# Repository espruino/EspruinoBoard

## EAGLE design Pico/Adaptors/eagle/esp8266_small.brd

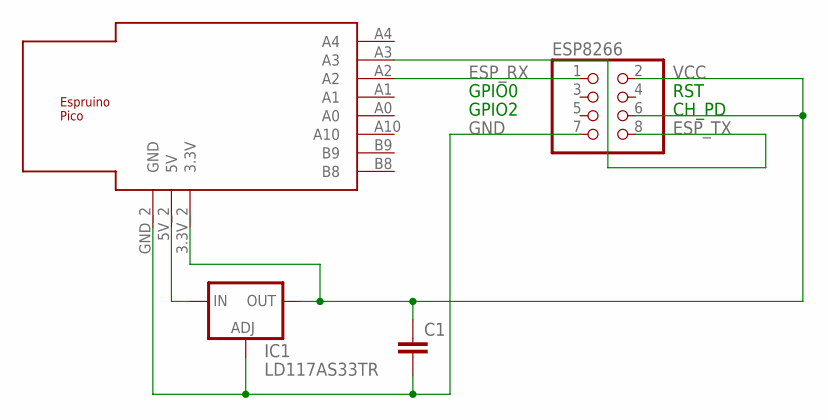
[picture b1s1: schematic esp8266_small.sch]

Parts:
C1: C-EUC1210; C1210
ESP8266: PINHD-2X4; 2X04
IC1: LD117AS33TR; SOT223
U$1: ESPRUINO_PICO_0.05

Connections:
ESP_RX: ESP8266.1, U$1.A2
ESP_TX: ESP8266.8, U$1.A3
GND: C1.2, ESP8266.7, IC1.1 (ADJ), U$1.GND_2 (GND)
unnamed: IC1.3 (IN), U$1.5V_2 (5V)
VCC: C1.1, ESP8266.2, ESP8266.6, IC1.4 (OUT), U$1.3.3V_2 (3.3V)

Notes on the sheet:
CH_PD
RST
GPIO0
GPIO2

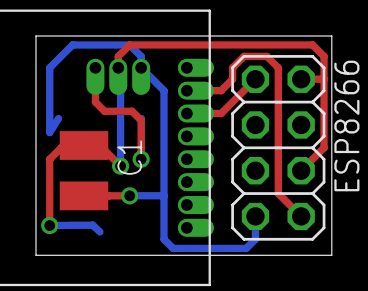
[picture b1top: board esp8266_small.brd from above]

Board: 2 copper layers, 16.4 x 12.2 mm, 4 parts (1 on the bottom side), 5 nets.

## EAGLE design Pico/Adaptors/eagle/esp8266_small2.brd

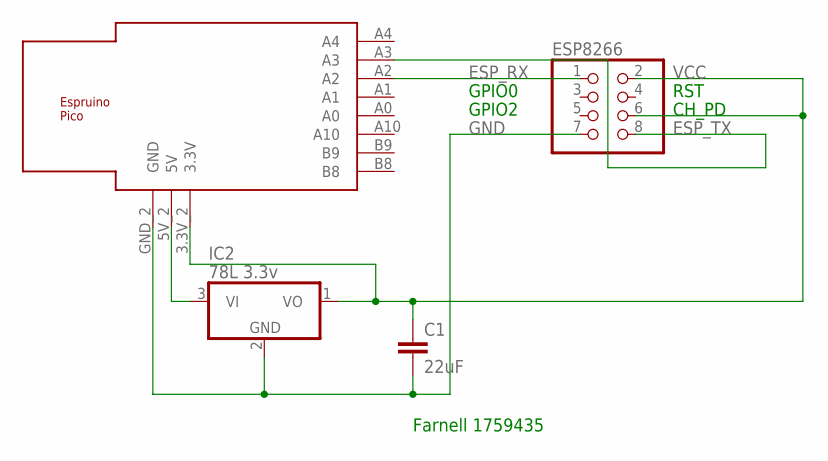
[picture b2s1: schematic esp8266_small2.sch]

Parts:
C1: 22uF; C1210
ESP8266: PINHD-2X4; 2X04
IC2: 78L 3.3v; TO92
U$1: ESPRUINO_PICO_0.05

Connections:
ESP_RX: ESP8266.1, U$1.A2
ESP_TX: ESP8266.8, U$1.A3
GND: C1.2, ESP8266.7, IC2.2 (GND), U$1.GND_2 (GND)
unnamed: IC2.3 (VI), U$1.5V_2 (5V)
VCC: C1.1, ESP8266.2, ESP8266.6, IC2.1 (VO), U$1.3.3V_2 (3.3V)

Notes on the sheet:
CH_PD
RST
GPIO0
GPIO2
Farnell 1759435

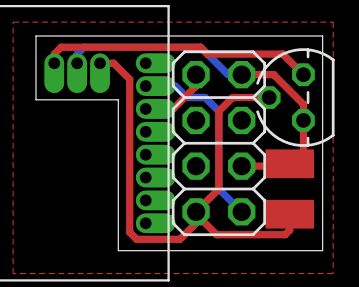
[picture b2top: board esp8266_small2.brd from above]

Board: 2 copper layers, 15.9 x 11.9 mm, 4 parts (0 on the bottom side), 5 nets.

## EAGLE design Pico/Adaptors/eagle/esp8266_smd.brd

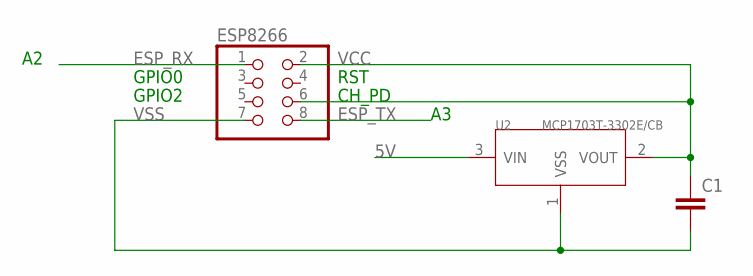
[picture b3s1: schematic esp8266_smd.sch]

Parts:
C1: C-EU025-050X050; C025-050X050
ESP8266: PINHD-2X4; 2X04
U2: MCP1703T-3302E/CB; SOT23

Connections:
5V: U2.3 (VIN)
ESP_RX: ESP8266.1
ESP_TX: ESP8266.8
VCC: C1.1, ESP8266.2, ESP8266.6, U2.2 (VOUT)
VSS: C1.2, ESP8266.7, U2.1 (VSS)

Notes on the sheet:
CH_PD
RST
GPIO0
GPIO2

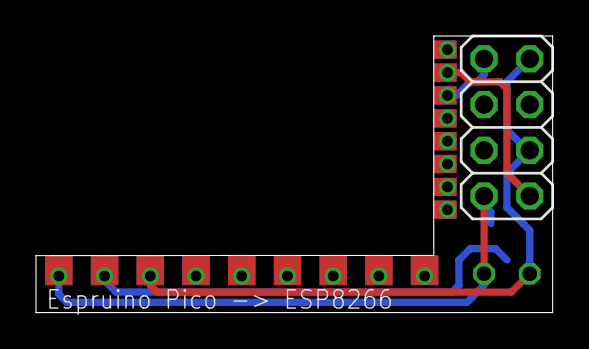
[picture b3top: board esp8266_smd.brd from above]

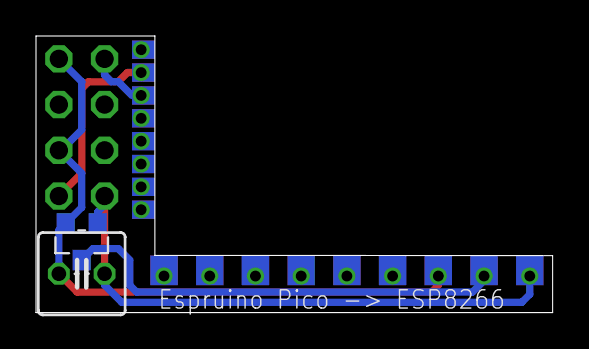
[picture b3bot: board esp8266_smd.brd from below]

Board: 2 copper layers, 28.7 x 15.4 mm, 3 parts (2 on the bottom side), 2 nets.

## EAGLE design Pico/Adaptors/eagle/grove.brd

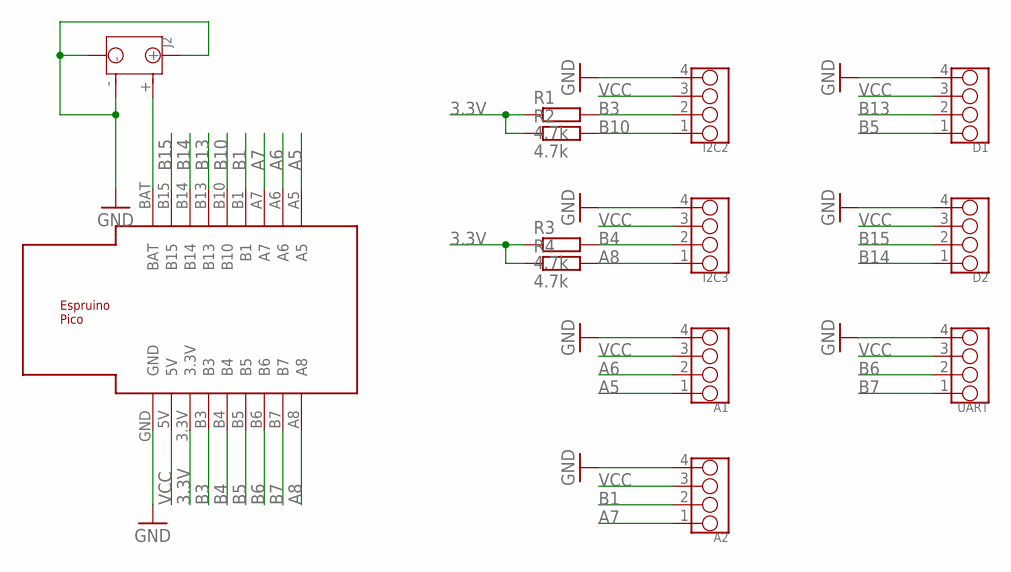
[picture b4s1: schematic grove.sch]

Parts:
A1, A2: GROVE-4P-2.0-3470130P1; 4P-2.0
D1, D2: GROVE-4P-2.0-3470130P1; 4P-2.0
I2C2, I2C3: GROVE-4P-2.0-3470130P1; 4P-2.0
J2: JST-2P-SMD-PW-3410050P1; 2P-SMD-2.0-90D
R1, R2, R3, R4: 4.7k; R0805
U$1: ESPRUINO_PICO_0.1
UART: GROVE-4P-2.0-3470130P1; 4P-2.0

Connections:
3.3V: R1.1, R2.1, R3.1, R4.1, U$1.3.3V
A5: A1.1, U$1.A5
A6: A1.2, U$1.A6
A7: A2.1, U$1.A7
A8: I2C3.1, R4.2, U$1.A8
B1: A2.2, U$1.B1
B3: I2C2.2, R1.2, U$1.B3
B4: I2C3.2, R3.2, U$1.B4
B5: D1.1, U$1.B5
B6: U$1.B6, UART.2
B7: U$1.B7, UART.1
B10: I2C2.1, R2.2, U$1.B10
B13: D1.2, U$1.B13
B14: D2.1, U$1.B14
B15: D2.2, U$1.B15
GND: A1.4, A2.4, D1.4, D2.4, I2C2.4, I2C3.4, J2.3, J2.4, J2.-, U$1.GND, UART.4
unnamed: J2.+, U$1.BAT
VCC: A1.3, A2.3, D1.3, D2.3, I2C2.3, I2C3.3, U$1.5V, UART.3

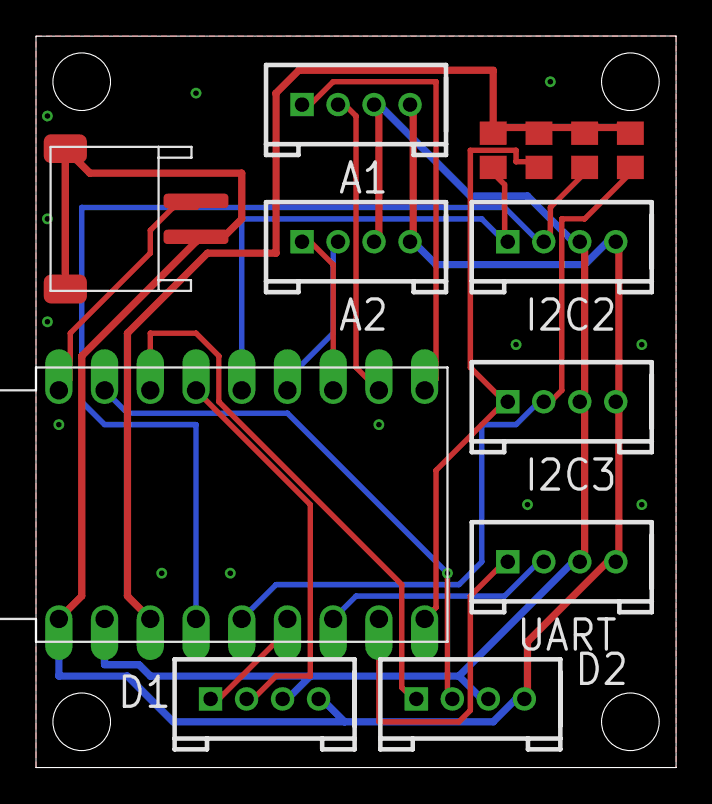
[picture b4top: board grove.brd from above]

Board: 2 copper layers, 35.6 x 40.6 mm, 13 parts (0 on the bottom side), 18 nets.

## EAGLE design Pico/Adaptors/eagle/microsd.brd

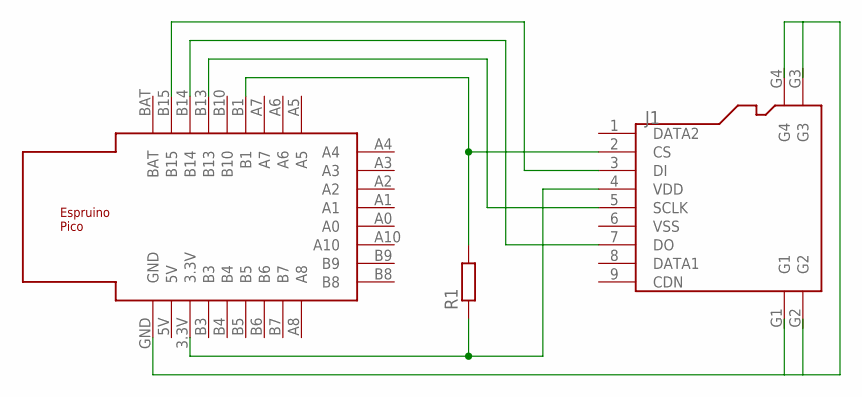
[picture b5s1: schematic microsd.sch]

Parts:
J1: MICRO-SDCARD-CONNECTOR-3300060P1; 9P-SMD-W/-RING
R1: R-EU_R1206; R1206
U$1: ESPRUINO_PICO_SMDONLY

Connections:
unnamed: J1.4 (VDD), R1.1, U$1.3.3V
unnamed: J1.3 (DI), U$1.B15
unnamed: J1.7 (DO), U$1.B14
unnamed: J1.5 (SCLK), U$1.B13
unnamed: J1.2 (CS), R1.2, U$1.B1

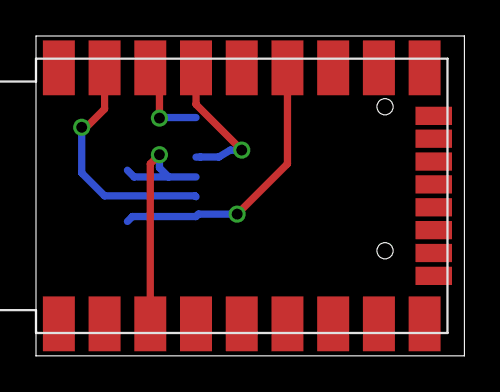
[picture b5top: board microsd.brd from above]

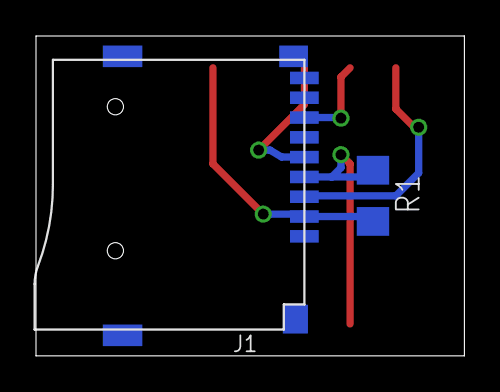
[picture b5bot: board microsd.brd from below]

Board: 2 copper layers, 23.8 x 17.8 mm, 3 parts (2 on the bottom side), 5 nets.

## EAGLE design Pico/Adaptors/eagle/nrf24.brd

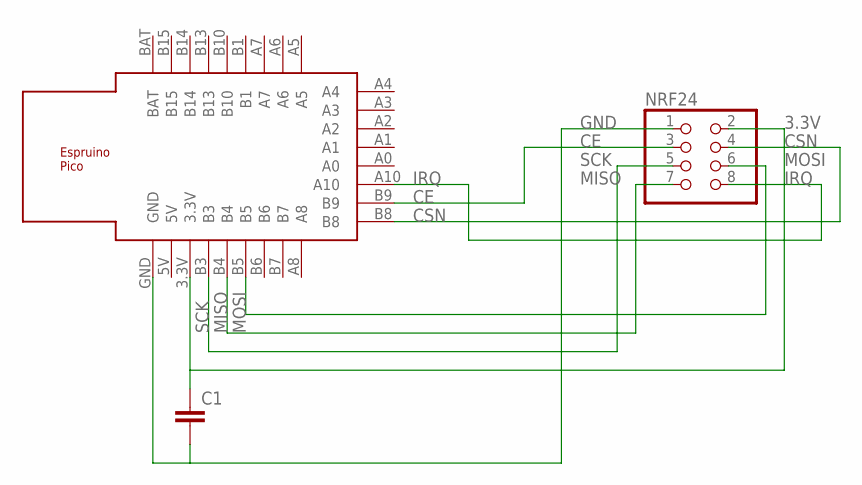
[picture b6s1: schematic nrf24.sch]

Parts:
C1: C-EUC1206; C1206
NRF24: PINHD-2X4; 2X04
U$2: ESPRUINO_PICO_HALFSMD

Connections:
3.3V: C1.1, NRF24.2, U$2.3.3V
CE: NRF24.3, U$2.B9
CSN: NRF24.4, U$2.B8
GND: C1.2, NRF24.1, U$2.GND
IRQ: NRF24.8, U$2.A10
MISO: NRF24.7, U$2.B4
MOSI: NRF24.6, U$2.B5
SCK: NRF24.5, U$2.B3

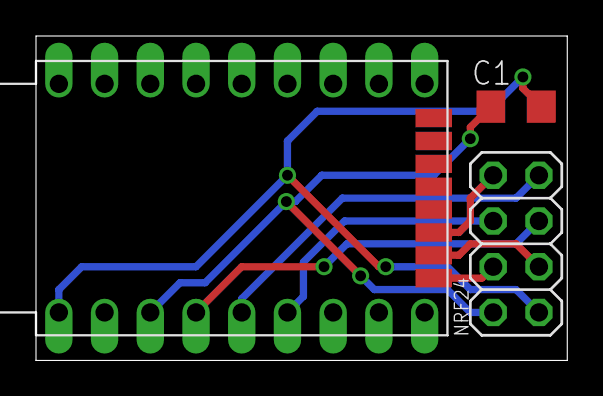
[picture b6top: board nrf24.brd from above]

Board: 2 copper layers, 29.5 x 18.0 mm, 3 parts (0 on the bottom side), 8 nets.
